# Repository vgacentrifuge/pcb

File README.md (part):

# VGA mixer PCB design
This repository contains the research and design work that went into the PCB
for our VGA mixer project in TDT4295 - computer project at NTNU, autumn 2022.

## Initial feasibility study
The [pdf](InitialFeasibilityStudy.pdf) contains the first research, before
the capabilities and requirements were fully fleshed out. In this repo,
we are working on the actual design.

## Project features
The VGA mixer is a device that takes two VGA inputs,
called "background" and "foreground", and outputs a single VGA video stream.

It should support the SVGA resolution 800x600 @ 60Hz and 16-bit color depth.
The colors are stored as (5,6,5)-bit RGB values internally.

On the board there are several buttons and an LCD screen,
allowing you to pick between different **modes**:
 - Showing only the foreground
 - Showing only the background
 - Overlaying with chroma keying appied to the foreground
 - Showing the foreground at 25%, 50% or 75% transparancy
 - Adding the colors (double exposure)

In addition to modes, the foreground can also be **scaled** and **translated**:
 - A button lets you pick between 100%, 50% and 25% size of the foreground.
 - Directional buttons allow you to move the foreground around

Finally, the foreground video input can be replaced by a still image loaded
from an SD card. Chroma keying can still be applied, to create borders or overlays.

TODO: Should we be able to save images, or is having a bank of overlays enough?

The LCD allows the user to orchestrate the modes and options to create quick
transitions, and saving states.

## Implementation overview
Both the background and foreground VGA signals get converted into digial pixel color values.
ADC chips do the conversion, and an FPGA reads the digital data.

The background video signal is never scaled or translated, and can be sent
almost directly out to the output DAC.
The output signal is just a few pixels behind the background.

The foreground gets buffered, either in SRAM or the FPGA's internal block RAM.
When the background signal is passing through the FPGA, it knows which pixel it is processing.
By checking its settings, it will know if and where the foreground framebuffer should be sampled.
Translations and scaling affect how the foreground overlays the background.

Scaling is done by doubling or quadrupling the current pixel coordinate (left shifting).
Translations are done by adding offsets. If the resulting pixel position
is still within the framebuffer bounds, it gets sampled.

Chroma key is handled by looking at the color chanels.
Transparancy is done by averaging the foreground and background layers.
To get 25% foreground, pixel = (fg+(fg<<1) + bg) >> 2, or something similar.
We don't want to do actual division.

User input is handled by an MCU, which is connected to the FPGA via SPI.
The MCU also handles the VGA input data pins, to communicate to our video sources
what resolution we support.

The SD card is also connected to the MCU over another SPI.
We use FAT32 formatted SD-cards, allowing the user to prepare overlays on their computer, saved as bmp.
See [this project here](https://create.arduino.cc/projecthub/SurtrTech/display-bmp-pictures-from-sd-card-on-tft-lcd-shield-f3074c).
The MCU does all file system work and image decoding. The LCD can be used to pick images by file name.
When selected, the foreground input gets ignored, and the FPGA fills the framebuffer with the image instead, sent over SPI.

In general, the MCU takes user input and uses SPI to send a state struct to the FPGA.
This means timed transitions, and switching between saved states, can be orchestrated from there.
Note that the MCU doesn't have enough RAM to store even a single frame.

## Components
This section contains the components we will need to place on the PCB.

### FPGA
We are working with the Artix-7 series, see the [Series Overview](https://docs.xilinx.com/v/u/en-US/ds180_7Series_Overview).

#### Dev-board
The [ARTY A7 development board](https://digilent.com/reference/programmable-logic/arty-a7/reference-manual) has an **ARTIX-7 XC7A35T** which has
 - 33280 logic cells
 - 50 blocks of 36Kib dual port block ram = 1 800Kib
 - 5 clock management tiles (CMTs), each with a phase-locked loop and mixed-mode clock manager
 - Programmable over JTAG or Quad-SPI Flash
 
The dev-board itself contains:
 - 256MB DDR3L with a 16-bit bus @ 667MHz
 - 16MB Quad-SPI Flash
 
#### On PCB
On the PCB we will use the **ARTIX-7 XC7A100T** in FTG256 package, which has already been procured.
 - 4,860 Kib of dual port block ram
 
See the data sheet for it [here](https://docs.xilinx.com/v/u/en-US/ds181_Artix_7_Data_Sheet),
and remember the user guides listed in the pcb lecture.

#### Voltages
The FPGA requires:
 - 1.0V (Vccint & Vccbram)
 - 1.8V (Vccaux)
 - 3.3V (Vcco) The standard signal voltage we use for I/O banks.

They must become ready in order, Vccint and Vccbram can rise together. 
For one bank, Vcco=1.8V, and the datasheet said it's fine to rise it together with Vccaux.

#### Required FPGA support components
In the datasheet they define that certain sets of **decoupling capacitors** should be connected to certain pins.
This is already included in the example schematic from the lecture.
Try to get them close to the pins on the actual PCB.

We also need a **configuration flash chip** on the board,
to program the FPGA on startup. See UG908 Appendix C.
We picked the one from the pcb lecture: [S25FL127SABMFV101](https://www.digikey.no/en/products/detail/cypress-semiconductor-corp/S25FL127SABMFV101/5788556).

#### FPGA's own clock signal
To not completly rely on the MCU's clockout,
The [arty schematic](https://digilent.com/reference/_media/arty:arty_sch.pdf) has and
[ASEM1-100.000MHZ-LC-T](https://no.mouser.com/ProductDetail/ABRACON/ASEM1-100.000MHZ-LC-T?qs=3KFUwL3kAg3Sbz4Re5NI5g%3D%3D), but it's not in stock.

We use the [EC2620TTS-100.000MTR](https://no.mouser.com/ProductDetail/Ecliptek-Abracon/EC2620TTS-100.000M-TR?qs=ZQxglWs2YhXyVb5B6v%252BGOw%3D%3D).

I checked the Xilinx Clocking Wizard, both MMCM and PLL will happily turn 100MHz into 160MHz.

#### Debug connector
The Debug connector from the lecture looks like the **14-pin F JTAG ILA connector**.
See [this website](https://developer.arm.com/documentation/100765/0000/Signal-descriptions/Debug-connectors/14-pin-F-JTAG-ILA-connector).
The pitch is 2mm, yes you read that right.
The component, through hole, can be found here:
[0878311411](https://www.digikey.no/en/products/detail/molex/0878311411/3313107).

See the example setup from the lecture (remember 2x 10k pullups).
However, this website says that pin 6 (TCK) is pulled down on their board,
**why is ours pulled up?** 

### SRAM
We need to calculate the required SRAM size.
With an 800x600=480 000 pixel grid, 16 bit color depth, it makes sense to
use a 512K x 16 bit SRAM. We do however also want to make the SRAM easy to address.

800 pixels of X-coordinate rounds up to 10 bits.
600 pixels of Y-coordinate also rounds up to 10 bits.
A 20 bit address means 2^20 = 1M x 16bit SRAM.

This size would also allow us to support 1024x768 (XGA),
but speed is a bigger issue. XGA has a pixel clock of 15.3ns / pixel.

To get good speed, we have looked at the syncronous 1M x 18b SRAM [CY7C1372KV33-200AXC](https://www.digikey.no/en/products/detail/cypress-semiconductor-corp/CY7C1372KV33-200AXC/5982740)
which supposedly costs 94kr per chip. It takes 3.3V.
With pipelining, the access time becomes 3ns,
with each operation delayed for two cycles.

The number of pins needed becomes:
 - 20 address pins
 - 18 data pins
 - write enable
 - clock
 - chip select
 - output enable

We use chip select to deselect, which when we don't need access.
The deselect is pipelined as well, allowing us to mix it into the operations.

We want to connect output enable to be sure that we never try to
write to th data line while it is being driven.
If we do everything perfectly, The data line is automatically tri-stated by writes,
but we want to be safe.

The rest, like output enable, clock enable, byte enable, advance etc. can all be pulled by the pcb.
This SRAM package does not expose JTAG pins.

### MCU
Available in the lab is the EFM32GG990F1024-BGA112
 - ARM Cortex M3
 - Flash: 1024kB
 - RAM: 128kB
 - USB support
 - ADC: 8 channels, 12 bit
 - DAC: 2 channels, 12 bit
 - SPI: 3
 - I2C: 2
 - GPIO: 87
 - 112 pin BGA package
 
For PCB considerations, see [SiLabs EFM32 AN0002](https://www.silabs.com/documents/public/application-notes/an0002.0-efm32-ezr32-series-0-hardware-design-considerations.pdf).
It includes decoupling capacitors. See Figure 3.1. EFM32 Series 0 Standard Decoupling Example.
Also add the 1 Ohm resistor from Figure 3.3.

#### MCU Debug connector

In the PCB lecture, they use the 2.54mm pitch legacy JTAG.
The debug conenctor is 20-pin header, shown in section 4 of AN0002.

Since we have a gecko with the modern connector, we can use the
modern [Cortex Debug+ETM Connector](https://documentation-service.arm.com/static/5fce6c49e167456a35b36af1).
It has 1.27mm pitch, we pick this through-hole one: [3220-20-0100-00](https://www.digikey.no/en/products/detail/cnc-tech/3220-20-0100-00/3883663).

#### MCU Clock circuit
By using an external crystal, as recommended, we can run the MCU at 48MHz.

<!--
This is simply buying a crystal oscillator.
The [FO7HSCDE48.0-T1](https://www.digikey.no/no/products/detail/fox-electronics/FO7HSCDE48-0-T1/12160237)
is 48MHz, SMD, and with 5mm and 2.5mm between the 4 pins, which at least isn't the smallest oscillator.
The datasheet also has recommended solder pad distance of at least 2.2 mm. Seems doable.
-->

The first chip we bought was in fact not a crystal, but an oscialltor chip using a crystal insternally.
We buy another one instead, see the schematic.

The AN0002 EFM32 hardware design considerations also mentions two capacitors.
The lecture uses 2x 12pF.

The FPGA can take the **clock out** signal from the EMF32GG as a clock input, and use phase-locked loops
to internally run faster clocks at rational multiples of the input.
We should also have a clock circuit on the FPGA side, so that we have two options.

### Connections
We use SPI between MCU and FPGA, and between MCU and SD-card. They can be fully independent.
For our SPI communication, the lecture tells us to add extra wires between the MCU and PCB for safety.

[I2C](https://en.wikipedia.org/wiki/I%C2%B2C) is "open drain", which means we must use pull-up resistors on the lines.
Calculations can be found in this [EFM32GG application note](https://www.silabs.com/documents/public/application-notes/AN0011.pdf).

We use I2C for the LCD, and I2C for the ADCs.
They both seem to like 400kHz, which means a 2kOhm resistor is common.
They both also want to be pulled up to 3.3V.

Between the boards, if we do make two PCBs, we want to connect them.
We can buy e.g. 2 of the 2x8 pin vertical male header per board [3020-16-0200-00](https://www.digikey.no/en/products/detail/cnc-tech/3020-16-0200-00/3441735).
And 2 of the female as well [PPPC082LJBN-RC](https://www.digikey.no/en/products/detail/sullins-connector-solutions/PPPC082LJBN-RC/776019).
These are both through-hole.

### Splitting the MCU and FPGA
We have considered splitting the PCB in half, to separate the MCU from the FPGA.
In practice we will probably not create two PCBs,
since clock lines shouldn't go through pins,
but it would be great to have a PCB that can be used
without the MCU physically on the board.

With SPI, we control the speed ourselves, so we can tune it down until it is stable,
depending on how the wiring is.

The SPI between the MCU and FPGA should have room to solder on a pin header.
The SPI clock is slower than the 48MHz clock-out from the MCU,
which should **not** have a pin header.
We also give the FPGA its own oscillator, to not depend on the MCU clock out.

The SPI lane for the SD card can also have holes for soldering on a pin header if desired.
The I2C buses for the ADCs and LCD screen should have pins,
and the keyboard matrix should have them.

### Power circuit
We base it on the PCB lecture. We need to power up the 1.0V, 1.8V and 3.3V in order.
The MCU and SD card use 3.3V, so does the SRAM.
The ADC uses 1.9V, and HSYNC and VSYNC must be level switched to / from 5V.

**Remember the jumpers** between the power circuit and rest of the board.
We buy a 2x5 male 2.54mm pin header [3020-10-0300-00](https://www.digikey.no/en/products/detail/cnc-tech/3020-10-0300-00/3441727), and
the 2x5 female jumper shunt, [69145-210LF](https://www.digikey.no/en/products/detail/amphenol-cs-fci/69145-210LF/1528094), with 3A rating per pin.

### SD-card & SD-card slot
We want a slot to be able to move the SD-card to and from a computer.
When connected, the MCU communicates via SPI to the card.
In addition to the 4 SPI pins, The SD-card takes a 3.3V VDD and ground.

See for instance [this website](https://www.electroniccircuitsdesign.com/pinout/sd-microsd-card-pinout.html) for pinout on the physical SD and microSD cards.

Note that [this SO-post](https://electronics.stackexchange.com/questions/496357/sd-card-via-spi-pull-up-resistors-or-dedicated-ic)
talks about pull-up resistors on all the data pins, we can do that too.

People seem to disagree, but hooking up a 10k Ohm resistor to each of DAT0-DAT3 and CMD seems good.
Also a 0.1 uF decoupling capacitor between Vcc and GND.

To easily solder, we can buy the [10067847-001RLF](https://www.digikey.no/no/products/detail/amphenol-cs-fci/10067847-001RLF/2283478).
It is full size SD, with solder pins visible

We should buy an SD card as well, the 512MB microSD [5252](https://www.digikey.no/en/products/detail/adafruit-industries-llc/5252/15841478) is cheap,
so buy at least one.

### LCD text output
A cheap 2 row x 16 char width LCD screen is [DFR0555](https://www.digikey.no/no/products/detail/dfrobot/DFR0555/9356340).
It is controlled over I2C.
8-bit address for LCD: 0x7C = 0b 0111 110X
8-bit address for backlight: 0xC0 = 0b 1100 000X
At 87mm x 32mm total, it is quite small. Each char is 2.96mm x 5.56mm.
Mouser doesn't have anything cheaper using I2C, so it's probably a good option.

### Input panel
We need to design a button layout that fits our functionality,
but also allows us to experiment after the PCB design is finalized.

We can use an off the shelf keyboard matrix, and re-label the keys.
Mouser stocks 81 of the 4x4 [3844](https://no.mouser.com/ProductDetail/Adafruit/3844?qs=qSfuJ%252Bfl%2Fd6WS5%252BJGim1hw%3D%3D).

### VGA ports
We need the physical VGA ports, as well as supporting components.
The speed we target is [SVGA 800x600@60Hz](http://tinyvga.com/vga-timing/800x600@60Hz).

The VGA connector itself is [described here](http://www.hardwarebook.info/VGA).
For VGA output we only really need to connect 5 pins, plus ground:
 - red, green, blue color (analog 0-0.7V, 75 Ohm)
 - horizontal sync, vertical sync (5V). See timing chart.

Note: While we are in the "porch" and sync pulse areas of the signal, the color values must all be 0V.
See for example the 2nd [Ben Eater VGA video](https://www.youtube.com/watch?v=uqY3FMuMuRo).

We also might want to connect the 3 DDC2B ports, in case we want to read info about the output monitor.
See the following sections about DAC and VGA Display Data Channel.

For inputs, we need to read those 5 signals, including the analog color signals (using ADCs).
We should also let the video sources get info about our board over I2C. See next sections.

As for the physical VGA ports, there is [L77HDE15SD1CH4FVGA](https://www.digikey.no/no/products/detail/amphenol-icc-commercial-products/L77HDE15SD1CH4FVGA/4888525) on digikey at 15kr a pop. Is has through-hole pins. Buy 9, 3 per PCB.

#### VGA Display Data Channel
The [DDC2B](https://en.wikipedia.org/wiki/Display_Data_Channel#DDC2) standard is an I2C protocol to communicate information about the "monitor" to the video source.

For the output port, we can connect the DDC pins to one of the MCU's I2C ports,
in case we want to read info about the screen.
NOTE: The I2C lines are open drain, and expect to be pulled up to 5V.
We will need a level shifter for the MCU to be able to use the I2C port.

##### VGA DDC level switches
The VGA standard expects 5V I2C over the SDA and SCL lines.
Both when we are slave and master, we want to support this.
Since all other I2C components use 3.3V, we level switch.

[This guide](https://cdn-shop.adafruit.com/datasheets/an97055.pdf)
shows how a single N-channel MOSFET does the trick.
We buy 2 per DDC I2C, 6 per board.
We pick the one they mention that is easiest to solder: [BSN20](https://www.digikey.no/en/products/detail/diodes-incorporated/BSN20-7/2756034).

<!--
For the three DDC channels, we can use one of
[771-LSF0102DCH](https://no.mouser.com/ProductDetail/Nexperia/LSF0102DCH?qs=zW32dvEIR3vhhHCS5E8Gjg%3D%3D)
for each.

If you are curious how open-drain interfaces, like I2C, work through it,
[this datasheet](https://www.ti.com/lit/ds/symlink/lsf0102.pdf?ts=1663455770501)
for a similar device has an example in section 9.2.
-->

#### VGA HSYNC VSYNC Level shifters
They come in at 5V, but must be 3.3V into the ADC.
Same applies to the output VGA, but the other way.
We don't use the DAC's HSYNC and VSYNC ports,
instead letting the FPGA control it.
It would be nice to support 1.8V input, since the rest of video out is at 1.8V.

For each ADC, and for the output, buy one
[771-LSF0102DCH](https://www.digikey.no/no/products/detail/nexperia-usa-inc/LSF0102DCH/13574967).

##### Input VGA ports: I2C EEPROMs
On our VGA inputs, we should respond to I2C read commands, to return 128-256 bytes of read only [Extended Display Identification Data](https://en.wikipedia.org/wiki/Extended_Display_Identification_Data).
See [this page](http://www.hardwarebook.info/VGA_(VESA_DDC)) for specifications.
The VGA DDC uses three pins: I2C data, I2C clock, and DC +5V delivered by the video source.
Our board must respond to the 7-bit I²C address 50h (also known as A0h and A1h in 8-bit).

To save having to use our MCU from needing to be a slave over the VGA ports, we can buy dirt cheep I2C EEPROMSs.
For instance [M24C02-WMN6TP](https://www.digikey.no/no/products/detail/stmicroelectronics/M24C02-WMN6TP/1663568),
in stock at Digikey.no, at 1,7kr a piece. They work at 2.5V - 5.5V, and we use one per VGA input = 6 for 3 boards.

Note: The EEPROMs technically support running on 5V,
and the VGA port has 5V supplied by the graphics card.
The reason we don't want to use it is that the graphics card
expects us to draw < 1mA when the monitor is on.

In DDC, the I2C master will try to read from address 0xA1 = 0b1010 0001.
This is perfect! The EEPROM listens for address 0b1010 XXXX, where
we configure the first 3 X's ourselves. The last bit is 1 for read and 0 for write.

##### I2C EEPROM support components
 - Vcc should be decoupled "usually of the order of 10 nF to 100 nF, close to the Vcc/Vss pins".
 - E0, E1 and E2 should be connected to ground, to listen to the correct address.
 
 - We should create a jumper thing to let the MCU be the programmer, if we ever need to change the EEPROM.
 - It should have 5 pins:
   - Vcc (3.3V)
   - Vss
   - SCL
   - SDA
   - Write enable (just connect to Vss to enable writing)
 
 Opposite to it there should be the same 5 pins comming from one of the MCU's I2C buses,
 e.g. the one used to configure the ADCs.
 
 To make the connector easy, we can use a 3x5 pin header, and have the MCU connected
 to the middle row, and jump either to the left or right.
 See [TSW-105-07-F-T](https://www.digikey.no/en/products/detail/samtec-inc/TSW-105-07-F-T/6692070).

#### Input VGA ADCs
The analog color inputs of each VGA input needs to become digital 6 or 5 bit values.
We can use ADCs with more bit depth than this, and then ignore the least significant bits.

The video ADC we looked at is the 3 channel x 10bit TI [TVP7002PZPR](https://no.mouser.com/ProductDetail/Texas-Instruments/TVP7002PZPR?qs=0OHPnBYoB%2FnBqXV%2Fq5aVXw%3D%3D)

It is configurable over I2C, things like gain, clamp and offset. Also programmable subpixel positioning.
It also has a PLL on the HSYNC, allowing it to generate a pixel clock for the FPGA VGA inputs.
The 40MHz on SVGA is well within the 12-165MHz range.

So: **we need to connect the ADCs to the MCU, to program them**.
Luckily, the chips have one bit of customizable address, so the options are:
 - 0xB8 = 0b10111000
 - 0xBA = 0b10111010
Remember that the last bit is 1 for read and 0 for write.
Notably, neither of these addresses collide with the 0xA0/0xA1 of the VGA DDC,
but you have to remember voltages.

The ADC needs 3.3V and **1.9V**!

The I/O is however 3.3V, so we can connect it to a "normal" FPGA bank.

But: VGA HSYNC and VSYNC are 5V signals. We can **not** pass those into the ADC!
See the HSYNC VSYNC Level shifter section above.

##### ADC support components
See the example setup in the datasheets.

- 1x (=2x) ADC support
     - 3x (=6x) Sync-on-green input disable: 1nF capacitor
     - 7x (=14x) 10nF capacitors for unused analog input
     - 1x (=2x) PLL pump
       - 1x (=2x) Resistor 1.5kOhm
       - 1x (=2x) Capacitor 4.7nF
       - 1x (=2x) Capacitor 0.1uF
   - 1x (=2x) I2C address choice: Resistor 2.2kOhm
   - 3x (=6x) Color inputs
     - 1x (=6x) 75 Ohm resistors
     - 1x (=6x) 0.1 uF capacitors
   - 1x (=2x) VSYNC parallel 1nF capacitor
   - even more stuff, just look at the suggested schematic

#### Output VGA DAC
When outputing analog color data, we don't want to use resistors, as they take space,
and the FPGA outputs are not the best at delivering DC current.

A nice DAC that Mouser stocks is  [THS8136IPHP](https://no.mouser.com/ProductDetail/Texas-Instruments/THS8136IPHP?qs=h8kCHL4kpM5MDIol0WiuLg%3D%3D)
It has 3 10-bit inputs named R, G and B, and 180MS/s.
For 800x600 @ 60Hz, a throughput of at least 40 MSPS is enough.
It takes 3.3V analog, and 1.8V digital.
**This means the FPGA pins delivering VGA out must be 1.8V**.
Luckily, when the Vcco is the same as Vccaux (1.8V), they can be ramped at the same time.

 - 0.1 uF decoupling capacitors near each power pin (3 of them)
 - 0.1 uF capacitors between COMP-AVdd and between VREF-AVss
 - R_FS between FSADJ and AVss. TODO
 - 3x 75 Ohm resistors, for each analog output? TODO

It also has [PCB Layout Guidelines](https://www.ti.com/lit/an/slea077/slea077.pdf?ts=1663284093618).
10x trace width clearance between analog inputs.
Everything close! Resistors, capacitors, analog output port.
TODO: ESD protection on the analog outputs is recommended.

#### Protection
We buy TVS diodes like the [PUSB3AB2DF](https://www.digikey.no/en/products/detail/nexperia-usa-inc/PUSB3AB2DFZ/12325057?s=N4IgTCBcDaIAoFUDKAhAzAQRWAIgMRAF0BfIA).

## Development components
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
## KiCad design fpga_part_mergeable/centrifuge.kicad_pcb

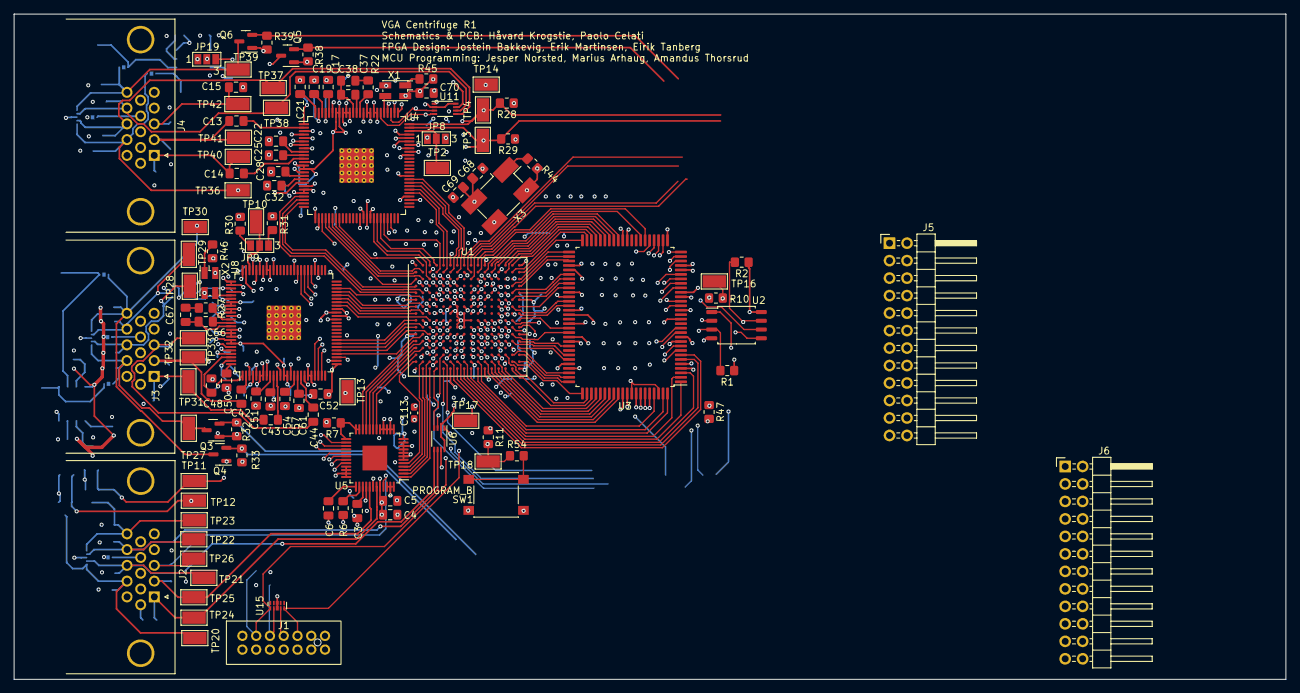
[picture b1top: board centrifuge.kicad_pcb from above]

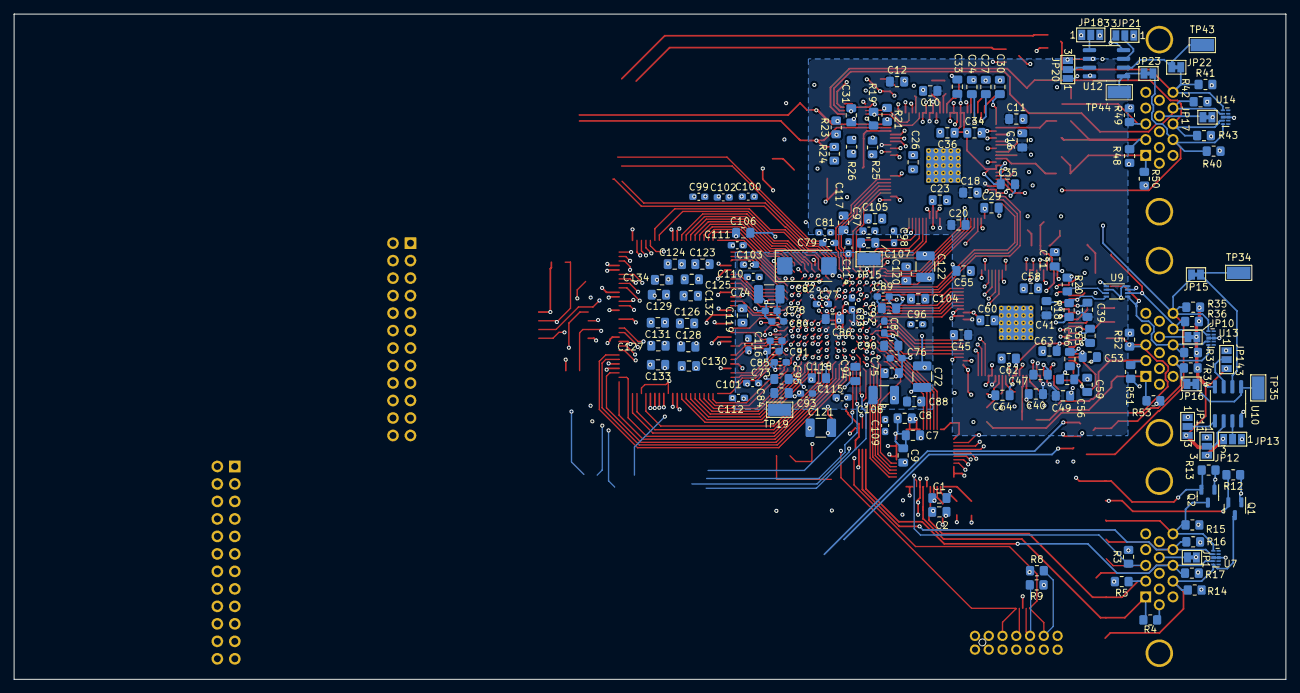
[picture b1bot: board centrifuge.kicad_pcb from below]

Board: 6 copper layers, 184.8 x 96.6 mm, 274 parts (163 on the bottom side), 265 nets.

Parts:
C1, C2, C7, C8: 10u; C_0805_2012Metric_Pad1.18x1.45mm_HandSolder
C3, C4, C5, C6, C9, C13, C14, C15, C20, C31, C36, C38, C42, C43, C44, C49, C60, C65, C67, C70, C71, C123, C124, C125, C126, C127, C128, C129, C130, C131, C132, C133, C134: 0.1u; C_0805_2012Metric_Pad1.18x1.45mm_HandSolder
C10, C11, C12, C16, C18, C23, C26, C29, C33, C34, C35, C39, C40, C41, C45, C47, C52, C55, C58, C62, C63, C64: 1u; C_0805_2012Metric_Pad1.18x1.45mm_HandSolder
C17, C19, C21, C22, C25, C28, C32, C46, C48, C50, C51, C54, C57, C61, C68: 10n; C_0805_2012Metric_Pad1.18x1.45mm_HandSolder
C24, C27, C30, C53, C56, C59: 1n; C_0805_2012Metric_Pad1.18x1.45mm_HandSolder
C37, C66: 4.7n; C_0805_2012Metric_Pad1.18x1.45mm_HandSolder
C69: 0.1u tantalum; C_0805_2012Metric_Pad1.18x1.45mm_HandSolder
C72, C108, C121, C122: 47u X5R/X7R; C_1210_3225Metric_Pad1.33x2.70mm_HandSolder
C73, C75, C84, C86, C88, C90, C92, C94, C104, C105, C106, C107, C117, C118, C119, C120: 4.7u; C_0805_2012Metric_Pad1.18x1.45mm_HandSolder
C74: 100u tantalum 1-40 mOhm or X5R/X7R; C_1210_3225Metric_Pad1.33x2.70mm_HandSolder
C76, C77, C78, C79, C80, C81, C83, C85, C87, C89, C91, C93, C95, C96, C97, C98, C99, C100, C101, C102, C103, C109, C110, C111, C112, C113, C114, C115, C116: 470n; C_0603_1608Metric_Pad1.08x0.95mm_HandSolder
C82: 330u tantalum 5-40 mOhm; CP_EIA-7343-31_Kemet-D_Pad2.25x2.55mm_HandSolder
J1: Conn_02x07_Odd_Even; 878311411
J2, J3, J4: Conn_01x15; L77HDE15SD1CH4FVGA
J5, J6: Conn_02x12_Odd_Even; PinHeader_2x12_P2.54mm_Horizontal
JP1, JP10, JP15, JP16, JP17, JP22, JP23: Jumper_2_Bridged; SolderJumper-2_P1.3mm_Bridged_Pad1.0x1.5mm
JP8, JP9: Jumper_3_Open; SolderJumper-3_P1.3mm_Open_Pad1.0x1.5mm_NumberLabels
JP11, JP12, JP13, JP14, JP18, JP19, JP20, JP21: SolderJumper_3_Bridged12; SolderJumper-3_P1.3mm_Open_Pad1.0x1.5mm_NumberLabels
Q1, Q2, Q3, Q4, Q5, Q6: BSN20; SOT-23
R1, R2, R11, R47: 4.7k; R_0805_2012Metric_Pad1.20x1.40mm_HandSolder
R3, R4, R5, R48, R49, R50, R51, R52, R53: 75; R_0805_2012Metric_Pad1.20x1.40mm_HandSolder
R6: 3.8k; R_0805_2012Metric_Pad1.20x1.40mm_HandSolder
R7, R23, R24, R25, R26, R28, R29, R30, R31: 2.2k; R_0805_2012Metric_Pad1.20x1.40mm_HandSolder
R8, R9, R44, R45, R46: 10k; R_0805_2012Metric_Pad1.20x1.40mm_HandSolder
R10, R54: 330; R_0805_2012Metric_Pad1.20x1.40mm_HandSolder
R12, R32, R38: vga_ddc_sda_pullup_l; R_0805_2012Metric_Pad1.20x1.40mm_HandSolder
R13, R33, R39: vga_ddc_scl_pullup_l; R_0805_2012Metric_Pad1.20x1.40mm_HandSolder
R14, R34, R40: vga_ddc_sda_pullup_h; R_0805_2012Metric_Pad1.20x1.40mm_HandSolder
R15, R35, R41: vga_ddc_scl_pullup_h; R_0805_2012Metric_Pad1.20x1.40mm_HandSolder
R16, R17, R18, R19, R20, R21, R36, R37, R42, R43: 1k; R_0805_2012Metric_Pad1.20x1.40mm_HandSolder
R22, R27: 1.5k; R_0805_2012Metric_Pad1.20x1.40mm_HandSolder
SW1: SW_MEC_5E; SW_Push_1P1T_NO_6x6mm_H9.5mm_modified
TP2, TP3, TP4, TP10, TP11, TP12, TP13, TP14, TP15, TP16, TP17, TP18, TP19, TP20, TP21, TP22, TP23, TP24, TP25, TP26, TP27, TP28, TP29, TP30, TP31, TP32, TP33, TP34, TP35, TP36, TP37, TP38, TP39, TP40, TP41, TP42, TP43, TP44: TestPoint; TestPoint_Keystone_5015_Micro-Minature
U1: XC7A100T-FTG256; Xilinx_FTG256
U2: S25FL127SABMFV10; SOIC-8_5.23x5.23mm_P1.27mm
U3: CY7C1370KV33; PQFP-100_14x20mm_P0.65mm
U4, U8: TVP7002; TQFP-100-1EP_14x14mm_P0.5mm_EP5x5mm_ThermalVias_elprint
U5: THS8136; LQFP-48-1EP_7x7mm_P0.5mm_EP3.6x3.6mm
U6, U9, U11: LSF0102; VSSOP-8_2.3x2mm_P0.5mm
U7, U13, U14: PESD4USB5B-TTS; Diodes_UDFN-10_1.0x2.5mm_P0.5mm
U10, U12: M24C02-WMN; SOIC-8_3.9x4.9mm_P1.27mm
U15: D5V0FS4U10LP; Diodes_UDFN-10_1.0x2.5mm_P0.5mm
X1, X2: ECS-2333-270-BN; Oscillator_SMD_EuroQuartz_XO32-4Pin_3.2x2.5mm_HandSoldering
X3: EC2620TTS-100.000MTR; Oscillator_SMD_EuroQuartz_XO91-4Pin_7.0x5.0mm_HandSoldering

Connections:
+1V0: C74.1, C76.1, C78.1, C80.1, C82.1, C83.1, C84.1, C85.1, C86.1, C87.1, C88.1, C89.1, C90.1, C91.1, C92.1, C93.1, C94.1, C95.1, TP15.1, TP17.1, TP19.1, U1.E10 (VCCBRAM), U1.F7 (VCCINT), U1.F9 (VCCINT), U1.F11 (VCCBRAM), U1.G6 (VCCINT), U1.H9 (VCCINT), U1.J6 (VCCINT), U1.K9 (VCCINT), U1.L8 (VCCINT)
+1V8_FPGA: C7.1, C8.1, C9.1, C72.1, C73.1, C75.1, C77.1, C79.1, C81.1, C96.1, C98.1, C100.1, C102.1, C104.1, C106.1, C108.1, J1.2, J5.8, R7.1, TP13.1, TP14.1, U1.G8 (VCCADC_0), U1.G10 (VCCAUX), U1.J10 (VCCAUX), U1.K11 (VCCAUX), U1.L10 (VCCAUX), U1.M3 (VCCO_34), U1.R4 (VCCO_34), U1.T1 (VCCO_34), U5.12 (DVDD), U6.2 (refA), U6.8 (EN), U9.2 (refA), U9.8 (EN), U11.2 (refA), U11.8 (EN)
+1V9_FPGA: C10.1, C11.1, C12.1, C16.1, C18.1, C20.1, C39.1, C40.1, C41.1, C45.1, C47.1, C49.1, J5.10, U4.4 (AVDD), U4.6 (AVDD), U4.7 (AVDD), U4.19 (AVDD), U4.39 (DVDD), U4.69 (DVDD), U4.84 (PLL_AVDD), U4.85 (PLL_AVDD), U8.4 (AVDD), U8.6 (AVDD), U8.7 (AVDD), U8.19 (AVDD), U8.39 (DVDD), U8.69 (DVDD), U8.84 (PLL_AVDD), U8.85 (PLL_AVDD)
+3V3A_FPGA: C33.1, C34.1, C35.1, C36.1, C62.1, C63.1, C64.1, C65.1, J5.6, U4.13 (A33VDD), U4.14 (A33VDD), U4.93 (A33VDD), U4.94 (A33VDD), U8.13 (A33VDD), U8.14 (A33VDD), U8.93 (A33VDD), U8.94 (A33VDD)
+3V3_FPGA: C1.1, C2.1, C4.1, C5.1, C23.1, C26.1, C29.1, C31.1, C52.1, C55.1, C58.1, C60.1, C68.1, C69.1, C70.1, C71.1, C97.1, C99.1, C101.1, C103.1, C105.1, C107.1, C109.1, C110.1, C111.1, C112.1, C113.1, C114.1, C115.1, C116.1, C117.1, C118.1, C119.1, C120.1, C121.1, C122.1, C123.1, C124.1, C125.1, C126.1, C127.1, C128.1, C129.1, C130.1, C131.1, C132.1, C133.1, C134.1, J5.4, Q1.1 (G), Q2.1 (G), Q3.1 (G), Q4.1 (G), Q5.1 (G), Q6.1 (G), R1.1, R2.1, R8.1, R9.1, R10.1, R11.1, R12.1, R13.1, R18.1, R19.1, R20.1, R21.1, R23.1, R24.1, R25.1, R28.1, R29.1, R30.1, R32.1, R33.1, R38.1, R39.1, R44.1, R45.1, R46.1, R47.1, U1.A6 (VCCO_35), U1.A16 (VCCO_15), U1.B3 (VCCO_35), U1.B13 (VCCO_15), U1.C10 (VCCO_15), U1.D7 (VCCO_35), U1.E4 (VCCO_35), U1.E7 (CFGBVS_0), U1.E14 (VCCO_15), U1.F1 (VCCO_35), U1.H15 (VCCO_15), U1.J2 (VCCO_35), U1.J12 (VCCO_15), U1.L6 (VCCO_0), U1.L16 (VCCO_14), U1.M9 (M0_0), U1.M13 (VCCO_14), U1.N10 (VCCO_14), U1.P7 (VCCO_14), U1.R14 (VCCO_14), U1.T11 (VCCO_14), U2.8 (VCC), U3.4 (VDDQ), U3.11 (VDDQ), U3.15 (VDD), U3.20 (VDDQ), U3.27 (VDDQ), U3.41 (VDD), U3.54 (VDDQ), U3.61 (VDDQ), U3.65 (VDD), U3.70 (VDDQ), U3.77 (VDDQ), U3.91 (VDD), U4.26 (IOVDD), U4.41 (IOVDD), U4.53 (IOVDD), U4.66 (IOVDD), U5.40 (AVDD), U5.44 (AVDD), U8.26 (IOVDD), U8.41 (IOVDD), U8.53 (IOVDD), U8.66 (IOVDD), X1.4 (VDD), X2.4 (VDD), X3.4 (VDD)
+5V_FPGA: J5.2, JP1.1 (A), JP10.1 (A), JP11.3 (B), JP12.3 (B), JP13.3 (B), JP14.3 (B), JP17.1 (A), JP18.3 (B), JP19.3 (B), JP20.3 (B), JP21.3 (B), R14.2, R15.2, R16.1, R17.1, R34.2, R35.2, R36.1, R37.1, R40.2, R41.2, R42.1, R43.1, U6.7 (refB), U9.7 (refB), U10.8 (VCC), U11.7 (refB), U12.8 (VCC)
/CONFIG_DONE: J5.21, R10.2, TP16.1, U1.H10 (DONE_0)
/INIT_B: J5.19, R47.2, U1.K10 (INIT_B_0)
/MCU_ADC0_RST: J5.5, U4.71 (RESETB)
/MCU_ADC1_RST: J5.11, U8.71 (RESETB)
/PROGRAM_B: J5.17, R11.2, R54.1, TP18.1, U1.L9 (PROGRAM_B_0)
/SCL_MCU_MASTER: J5.9, Q2.2 (S), R13.2, R24.2, R29.2, TP3.1, TP11.1, U4.74 (SCL), U8.74 (SCL)
/SCL_MCU_SL0: J5.1, Q6.2 (S), R39.2
/SCL_MCU_SL1: J5.13, Q4.2 (S), R33.2
/SDA_MCU_MASTER: J5.7, Q1.2 (S), R12.2, R23.2, R28.2, TP4.1, TP12.1, U4.75 (SDA), U8.75 (SDA)
/SDA_MCU_SL0: J5.3, Q5.2 (S), R38.2
/SDA_MCU_SL1: J5.15, Q3.2 (S), R32.2
/fpga_part/AUXIO1: J6.17, U1.K12 (IO_0_14)
/fpga_part/AUXIO2: J6.19, U1.M14 (IO_L4N_T0_D05_14)
/fpga_part/AUXIO3: J6.21, U1.K13 (IO_L5P_T0_D06_14)
/fpga_part/AUXIO4: J6.23, U1.M12 (IO_L6N_T0_D08_VREF_14)
/fpga_part/AUXIO5: J6.24, U1.P10 (IO_L14P_T2_SRCC_14)
/fpga_part/AUXIO6: J6.22, U1.P11 (IO_L14N_T2_SRCC_14)
/fpga_part/AUXIO7: J6.20, U1.N9 (IO_L18P_T2_A12_D28_14)
/fpga_part/AUXIO8: J6.18, U1.P9 (IO_L18N_T2_A11_D27_14)
/fpga_part/AUXIO9: J6.16, U1.R5 (IO_L23P_T3_A03_D19_14)
/fpga_part/AUXIO10: J6.14, U1.T5 (IO_L23N_T3_A02_D18_14)
/fpga_part/AUXIO11: J6.12, U1.P6 (IO_25_14)
/fpga_part/AUXIO12: J6.10, U1.J15 (IO_L23P_T3_FOE_B_15)
/fpga_part/AUXIO13: J6.8, U1.B9 (IO_L3P_T0_DQS_AD1P_15)
/fpga_part/AUXIO14: J6.6, U1.A9 (IO_L2N_T0_AD8N_15)
/fpga_part/AUXIO15: J6.4, U1.A8 (IO_L2P_T0_AD8P_15)
/fpga_part/AUXIO16: J6.2, U1.C9 (IO_L1N_T0_AD0N_15)
/fpga_part/AUXIO17L: J6.1, U1.P5 (IO_L10P_T1_34)
/fpga_part/AUXIO18: J6.3, U1.C4 (IO_L12N_T1_MRCC_35)
/fpga_part/AUXIO19: J6.5, U1.D4 (IO_L12P_T1_MRCC_35)
/fpga_part/AUXIO20: J6.7, U1.D5 (IO_L6N_T0_VREF_35)
/fpga_part/AUXIO21: J6.9, U1.D6 (IO_L6P_T0_35)
/fpga_part/AUXIO22: J6.11, U1.C6 (IO_L5N_T0_AD13N_35)
/fpga_part/AUXIO23: J6.13, U1.C7 (IO_L5P_T0_AD13P_35)
/fpga_part/AUXIO24: J6.15, U1.E6 (IO_0_35)
/fpga_part/config_sram/CCLK: U1.E8 (CCLK_0), U2.6 (CLK)
/fpga_part/config_sram/GCLK100: U1.C13 (IO_L12N_T1_MRCC_15), X3.3 (OUT)
/fpga_part/config_sram/IO0: U1.J13 (IO_L1P_T0_D00_MOSI_14), U2.5 (SI/IO0)
/fpga_part/config_sram/IO1: U1.J14 (IO_L1N_T0_D01_DIN_14), U2.2 (SO/IO1)
/fpga_part/config_sram/IO2: R1.2, U1.K15 (IO_L2P_T0_D02_14), U2.3 (n_WP/IO2)
/fpga_part/config_sram/IO3: R2.2, U1.K16 (IO_L2N_T0_D03_14), U2.7 (n_HOLD/IO3)
/fpga_part/config_sram/SRAM_A0: U1.B10 (IO_L4P_T0_15), U3.37 (A0)
/fpga_part/config_sram/SRAM_A1: U1.A10 (IO_L3N_T0_DQS_AD1N_15), U3.36 (A1)
/fpga_part/config_sram/SRAM_A2: U1.C11 (IO_L11P_T1_SRCC_15), U3.35 (A)
/fpga_part/config_sram/SRAM_A3: U1.C12 (IO_L11N_T1_SRCC_15), U3.34 (A)
/fpga_part/config_sram/SRAM_A4: U1.D11 (IO_L14N_T2_SRCC_15), U3.33 (A)
/fpga_part/config_sram/SRAM_A5: U1.E12 (IO_L13P_T2_MRCC_15), U3.32 (A)
/fpga_part/config_sram/SRAM_A6: U1.B12 (IO_L5P_T0_AD9P_15), U3.44 (A)
/fpga_part/config_sram/SRAM_A7: U1.A13 (IO_L7P_T1_AD2P_15), U3.45 (A)
/fpga_part/config_sram/SRAM_A8: U1.A14 (IO_L7N_T1_AD2N_15), U3.46 (A)
/fpga_part/config_sram/SRAM_A9: U1.B14 (IO_L8N_T1_AD10N_15), U3.47 (A)
/fpga_part/config_sram/SRAM_A10: U1.A15 (IO_L9N_T1_DQS_AD3N_15), U3.48 (A)
/fpga_part/config_sram/SRAM_A11: U1.B15 (IO_L9P_T1_DQS_AD3P_15), U3.49 (A)
/fpga_part/config_sram/SRAM_A12: U1.B16 (IO_L10N_T1_AD11N_15), U3.50 (A)
/fpga_part/config_sram/SRAM_A13: U1.T9 (IO_L22P_T3_A05_D21_14), U3.100 (A)
/fpga_part/config_sram/SRAM_A14: U1.T10 (IO_L22N_T3_A04_D20_14), U3.99 (A)
/fpga_part/config_sram/SRAM_A15: U1.T14 (IO_L10P_T1_D14_14), U3.84 (A)
/fpga_part/config_sram/SRAM_A16: U1.T15 (IO_L10N_T1_D15_14), U3.83 (A)
/fpga_part/config_sram/SRAM_A17: U1.P14 (IO_L12N_T1_MRCC_14), U3.82 (A)
/fpga_part/config_sram/SRAM_A18: U1.R15 (IO_L9P_T1_DQS_14), U3.81 (A)
/fpga_part/config_sram/SRAM_A19: U1.B11 (IO_L4N_T0_15), U3.42 (NC(72))
/fpga_part/config_sram/SRAM_A20: U1.A12 (IO_L5N_T0_AD9N_15), U3.43 (NC(36))
/fpga_part/config_sram/SRAM_ADV_LD: U1.R13 (IO_L16P_T2_CSI_B_14), U3.85 (ADV/~LD)
/fpga_part/config_sram/SRAM_CE1: U1.P8 (IO_L20P_T3_A08_D24_14), U3.92 (~CE3), U3.98 (~CE1)
/fpga_part/config_sram/SRAM_CE2: U1.R10 (IO_L17P_T2_A14_D30_14), U3.97 (CE2)
/fpga_part/config_sram/SRAM_CEN: U1.R12 (IO_L15P_T2_DQS_RDWR_B_14), U3.87 (~CEN)
/fpga_part/config_sram/SRAM_CLK: U1.R11 (IO_L17N_T2_A13_D29_14), U3.89 (CLK)
/fpga_part/config_sram/SRAM_D0: U1.H16 (IO_L22P_T3_A17_15), U3.63 (DQa)
/fpga_part/config_sram/SRAM_D1: U1.G15 (IO_L24N_T3_RS0_15), U3.62 (DQa)
/fpga_part/config_sram/SRAM_D2: U1.G16 (IO_L22N_T3_A16_15), U3.59 (DQa)
/fpga_part/config_sram/SRAM_D3: U1.F15 (IO_L18P_T2_A24_15), U3.58 (DQa)
/fpga_part/config_sram/SRAM_D4: U1.E16 (IO_L17P_T2_A26_15), U3.57 (DQa)
/fpga_part/config_sram/SRAM_D5: U1.E15 (IO_L18N_T2_A23_15), U3.56 (DQa)
/fpga_part/config_sram/SRAM_D6: U1.D16 (IO_L17N_T2_A25_15), U3.53 (DQa)
/fpga_part/config_sram/SRAM_D7: U1.D15 (IO_L15N_T2_DQS_ADV_B_15), U3.52 (DQa)
/fpga_part/config_sram/SRAM_D8: U1.C16 (IO_L10P_T1_AD11P_15), U3.51 (DQPa)
/fpga_part/config_sram/SRAM_D9: U1.C14 (IO_L8P_T1_AD10P_15), U3.30 (DQPd)
/fpga_part/config_sram/SRAM_D10: U1.D13 (IO_L12P_T1_MRCC_15), U3.29 (DQd)
/fpga_part/config_sram/SRAM_D11: U1.D14 (IO_L15P_T2_DQS_15), U3.28 (DQd)
/fpga_part/config_sram/SRAM_D12: U1.E13 (IO_L13N_T2_MRCC_15), U3.25 (DQd)
/fpga_part/config_sram/SRAM_D13: U1.F13 (IO_L16N_T2_A27_15), U3.24 (DQd)
/fpga_part/config_sram/SRAM_D14: U1.F14 (IO_L21N_T3_DQS_A18_15), U3.23 (DQd)
/fpga_part/config_sram/SRAM_D15: U1.G14 (IO_L21P_T3_DQS_15), U3.22 (DQd)
/fpga_part/config_sram/SRAM_D16: U1.H14 (IO_L24P_T3_RS1_15), U3.19 (DQd)
/fpga_part/config_sram/SRAM_D17: U1.H13 (IO_L20N_T3_A19_15), U3.18 (DQd)
/fpga_part/config_sram/SRAM_D18: U1.L14 (IO_L4P_T0_D04_14), U3.13 (DQc)
/fpga_part/config_sram/SRAM_D19: U1.L13 (IO_L5N_T0_D07_14), U3.12 (DQc)
/fpga_part/config_sram/SRAM_D20: U1.N13 (IO_L11P_T1_SRCC_14), U3.9 (DQc)
/fpga_part/config_sram/SRAM_D21: U1.P13 (IO_L11N_T1_SRCC_14), U3.8 (DQc)
/fpga_part/config_sram/SRAM_D22: U1.R6 (IO_L24P_T3_A01_D17_14), U3.7 (DQc)
/fpga_part/config_sram/SRAM_D23: U1.T7 (IO_L21P_T3_DQS_14), U3.6 (DQc)
/fpga_part/config_sram/SRAM_D24: U1.R7 (IO_L24N_T3_A00_D16_14), U3.3 (DQc)
/fpga_part/config_sram/SRAM_D25: U1.R8 (IO_L20N_T3_A07_D23_14), U3.2 (DQc)
/fpga_part/config_sram/SRAM_D26: U1.T8 (IO_L21N_T3_DQS_A06_D22_14), U3.1 (DQPc)
/fpga_part/config_sram/SRAM_D27: U1.R16 (IO_L9N_T1_DQS_D13_14), U3.80 (DQPb)
/fpga_part/config_sram/SRAM_D28: U1.P16 (IO_L8N_T1_D12_14), U3.79 (DQb)
/fpga_part/config_sram/SRAM_D29: U1.P15 (IO_L8P_T1_D11_14), U3.78 (DQb)
/fpga_part/config_sram/SRAM_D30: U1.N16 (IO_L7N_T1_D10_14), U3.75 (DQb)
/fpga_part/config_sram/SRAM_D31: U1.M15 (IO_L3N_T0_DQS_EMCCLK_14), U3.74 (DQb)
/fpga_part/config_sram/SRAM_D33: U1.M16 (IO_L7P_T1_D09_14), U3.72 (DQb)
/fpga_part/config_sram/SRAM_D34: U1.L15 (IO_L3P_T0_DQS_PUDC_B_14), U3.69 (DQb)
/fpga_part/config_sram/SRAM_D35: U1.J16 (IO_L23N_T3_FWE_B_15), U3.68 (DQb)
/fpga_part/config_sram/SRAM_OE: U1.T13 (IO_L16N_T2_A15_D31_14), U3.86 (~OE)
/fpga_part/config_sram/SRAM_WE: U1.T12 (IO_L15N_T2_DQS_DOUT_CSO_B_14), U3.88 (~WE)
/fpga_part/config_sram/n_CONFIG_CS: U1.L12 (IO_L6P_T0_FCS_B_14), U2.1 (~CS)
/fpga_part/e1/B: C44.2, J3.3, R52.1, TP33.1
/fpga_part/e1/B5: U1.J1 (IO_L22N_T3_35), U8.33 (B_5)
/fpga_part/e1/B6: U1.K2 (IO_L24N_T3_35), U8.32 (B_6)
/fpga_part/e1/B7: U1.K1 (IO_L22P_T3_35), U8.31 (B_7)
/fpga_part/e1/B8: U1.L3 (IO_L23P_T3_35), U8.30 (B_8)
/fpga_part/e1/B9: U1.L2 (IO_L23N_T3_35), U8.29 (B_9)
/fpga_part/e1/DCLK_OUT: U1.F5 (IO_L13P_T2_MRCC_35), U8.28 (DATACLK)
/fpga_part/e1/FIDOUT: U1.J4 (IO_L19N_T3_VREF_35), U8.22 (FIDOUT)
/fpga_part/e1/G: C42.2, J3.2, R51.1, TP32.1
/fpga_part/e1/G4: U1.F2 (IO_L15P_T2_DQS_35), U8.48 (G_4)
/fpga_part/e1/G5: U1.G2 (IO_L17P_T2_35), U8.47 (G_5)
/fpga_part/e1/G6: U1.G1 (IO_L17N_T2_35), U8.46 (G_6)
/fpga_part/e1/G7: U1.H2 (IO_L20P_T3_35), U8.45 (G_7)
/fpga_part/e1/G8: U1.H1 (IO_L20N_T3_35), U8.44 (G_8)
/fpga_part/e1/G9: U1.J3 (IO_L21P_T3_DQS_35), U8.43 (G_9)
/fpga_part/e1/HSIN: R18.2, U8.81 (HSYNC_A), U9.4 (A2)
/fpga_part/e1/HSOUT: U1.K3 (IO_L24P_T3_35), U8.24 (HSOUT)
/fpga_part/e1/R: C43.2, J3.1, R53.1, TP31.1
/fpga_part/e1/R5: U1.H4 (IO_L18N_T2_35), U8.59 (R_5)
/fpga_part/e1/R6: U1.H5 (IO_L18P_T2_35), U8.58 (R_6)
/fpga_part/e1/R7: U1.H3 (IO_L21N_T3_DQS_35), U8.57 (R_7)
/fpga_part/e1/R8: U1.G4 (IO_L16N_T2_35), U8.56 (R_8)
/fpga_part/e1/R9: U1.F4 (IO_L14P_T2_SRCC_35), U8.55 (R_9)
/fpga_part/e1/VSIN: R20.2, U8.78 (VSYNC_A), U9.3 (A1)
/fpga_part/e1/VSOUT: U1.J5 (IO_L19P_T3_35), U8.23 (VSOUT)
/fpga_part/e2/B: C15.2, J4.3, R49.1, TP42.1
/fpga_part/e2/B5: U1.A2 (IO_L8N_T1_AD14N_35), U4.33 (B_5)
/fpga_part/e2/B6: U1.B2 (IO_L8P_T1_AD14P_35), U4.32 (B_6)
/fpga_part/e2/B7: U1.B1 (IO_L9N_T1_DQS_AD7N_35), U4.31 (B_7)
/fpga_part/e2/B8: U1.C2 (IO_L7N_T1_AD6N_35), U4.30 (B_8)
/fpga_part/e2/B9: U1.C1 (IO_L9P_T1_DQS_AD7P_35), U4.29 (B_9)
/fpga_part/e2/DCLK_OUT: U1.E5 (IO_L13N_T2_MRCC_35), U4.28 (DATACLK)
/fpga_part/e2/FIDOUT: U1.E1 (IO_L15N_T2_DQS_35), U4.22 (FIDOUT)
/fpga_part/e2/G: C13.2, J4.2, R48.1, TP41.1
/fpga_part/e2/G4: U1.D3 (IO_L11N_T1_SRCC_35), U4.48 (G_4)
/fpga_part/e2/G5: U1.E3 (IO_L11P_T1_SRCC_35), U4.47 (G_5)
/fpga_part/e2/G6: U1.B4 (IO_L4P_T0_35), U4.46 (G_6)
/fpga_part/e2/G7: U1.A4 (IO_L3N_T0_DQS_AD5N_35), U4.45 (G_7)
/fpga_part/e2/G8: U1.A3 (IO_L4N_T0_35), U4.44 (G_8)
/fpga_part/e2/G9: U1.C3 (IO_L7P_T1_AD6P_35), U4.43 (G_9)
/fpga_part/e2/HSIN: R19.2, U4.81 (HSYNC_A), U11.4 (A2)
/fpga_part/e2/HSOUT: U1.D1 (IO_L10N_T1_AD15N_35), U4.24 (HSOUT)
/fpga_part/e2/R: C14.2, J4.1, R50.1, TP40.1
/fpga_part/e2/R5: U1.B7 (IO_L1P_T0_AD4P_35), U4.59 (R_5)
/fpga_part/e2/R6: U1.A7 (IO_L1N_T0_AD4N_35), U4.58 (R_6)
/fpga_part/e2/R7: U1.B6 (IO_L2P_T0_AD12P_35), U4.57 (R_7)
/fpga_part/e2/R8: U1.B5 (IO_L2N_T0_AD12N_35), U4.56 (R_8)
/fpga_part/e2/R9: U1.A5 (IO_L3P_T0_DQS_AD5P_35), U4.55 (R_9)
/fpga_part/e2/VSIN: R21.2, U4.78 (VSYNC_A), U11.3 (A1)
/fpga_part/e2/VSOUT: U1.E2 (IO_L10P_T1_AD15P_35), U4.23 (VSOUT)
/fpga_part/e3/SCL: JP15.1 (A), TP34.1, U10.6 (SCL)
/fpga_part/e3/SDA: JP16.1 (A), TP35.1, U10.5 (SDA)
/fpga_part/e4/SCL: JP22.1 (A), TP43.1, U12.6 (SCL)
/fpga_part/e4/SDA: JP23.1 (A), TP44.1, U12.5 (SDA)
/fpga_part/e/B5: U1.R1 (IO_L7N_T1_34), U5.5 (B5)
/fpga_part/e/B6: U1.R2 (IO_L7P_T1_34), U5.4 (B6)
/fpga_part/e/B7: U1.T2 (IO_L8N_T1_34), U5.3 (B7)
/fpga_part/e/B8: U1.R3 (IO_L8P_T1_34), U5.2 (B8)
/fpga_part/e/B9: U1.T3 (IO_L9N_T1_DQS_34), U5.1 (B9)
/fpga_part/e/B_OUT: J2.3, R3.1, TP26.1, U5.45 (AB)
/fpga_part/e/COMP: C3.1, U5.39 (COMP)
/fpga_part/e/DAC_CLK: U1.L4 (IO_L1P_T0_34), U5.26 (CLK)
/fpga_part/e/FSADJ: R6.1, U5.38 (FSADJ)
/fpga_part/e/G4: U1.M5 (IO_L6P_T0_34), U5.32 (G4)
/fpga_part/e/G5: U1.P4 (IO_L5P_T0_34), U5.31 (G5)
/fpga_part/e/G6: U1.N4 (IO_L6N_T0_VREF_34), U5.30 (G6)
/fpga_part/e/G7: U1.P3 (IO_L5N_T0_34), U5.29 (G7)
/fpga_part/e/G8: U1.M4 (IO_L1N_T0_34), U5.28 (G8)
/fpga_part/e/G9: U1.N3 (IO_L3P_T0_DQS_34), U5.27 (G9)
/fpga_part/e/G_OUT: J2.2, R5.1, TP25.1, U5.41 (AG)
/fpga_part/e/R5: U1.P1 (IO_L4N_T0_34), U5.18 (R5)
/fpga_part/e/R6: U1.N2 (IO_L3N_T0_DQS_34), U5.19 (R6)
/fpga_part/e/R7: U1.N1 (IO_L4P_T0_34), U5.20 (R7)
/fpga_part/e/R8: U1.M2 (IO_L2P_T0_34), U5.21 (R8)
/fpga_part/e/R9: U1.M1 (IO_L2N_T0_34), U5.22 (R9)
/fpga_part/e/R_OUT: J2.1, R4.1, TP24.1, U5.43 (AR)
/fpga_part/e/SYNC_T: R7.2, U5.23 (~BLANK), U5.24 (~SYNC), U5.25 (SYNC_T)
/fpga_part/e/VREF: C6.1, U5.37 (VREF)
/fpga_part/fpga_core/HSYNC_OUT0: U1.L5 (IO_0_34), U6.3 (A1)
/fpga_part/fpga_core/VSYNC_OUT0: U1.T4 (IO_L9P_T1_DQS_34), U6.4 (A2)
/fpga_part/pwr_jtag/TCK: J1.6, R9.2, U1.L7 (TCK_0), U15.2 (CH2)
/fpga_part/pwr_jtag/TDI: J1.10, U1.N7 (TDI_0), U15.5 (CH4)
/fpga_part/pwr_jtag/TDO: J1.8, U1.N8 (TDO_0), U15.4 (CH3)
/fpga_part/pwr_jtag/TMS: J1.4, R8.2, U1.M7 (TMS_0), U15.1 (CH1)
/fpga_part/vga_interface1/HSYNC_H: J3.13, R37.2, TP28.1, U9.5 (B2), U13.4 (CH3)
/fpga_part/vga_interface1/SCL_H: J3.15, JP15.2 (B), Q4.3 (D), R35.1, TP30.1, U13.1 (CH1)
/fpga_part/vga_interface1/SDA_H: J3.12, JP16.2 (B), Q3.3 (D), R34.1, TP27.1, U13.5 (CH4)
/fpga_part/vga_interface1/VSYNC_H: J3.14, R36.2, TP29.1, U9.6 (B1), U13.2 (CH2)
/fpga_part/vga_interface2/HSYNC_H: J4.13, R43.2, TP37.1, U11.5 (B2), U14.4 (CH3)
/fpga_part/vga_interface2/SCL_H: J4.15, JP22.2 (B), Q6.3 (D), R41.1, TP39.1, U14.1 (CH1)
/fpga_part/vga_interface2/SDA_H: J4.12, JP23.2 (B), Q5.3 (D), R40.1, TP36.1, U14.5 (CH4)
/fpga_part/vga_interface2/VSYNC_H: J4.14, R42.2, TP38.1, U11.6 (B1), U14.2 (CH2)
/fpga_part/vga_interface/HSYNC_H: J2.13, R17.2, TP21.1, U6.5 (B2), U7.4 (CH3)
/fpga_part/vga_interface/SCL_H: J2.15, Q2.3 (D), R15.1, TP23.1, U7.1 (CH1)
/fpga_part/vga_interface/SDA_H: J2.12, Q1.3 (D), R14.1, TP20.1, U7.5 (CH4)
/fpga_part/vga_interface/VSYNC_H: J2.14, R16.2, TP22.1, U6.6 (B1), U7.2 (CH2)
EP_GND: C1.2, C2.2, C3.2, C4.2, C5.2, C6.2, C7.2, C8.2, C9.2, C10.2, C11.2, C12.2, C16.2, C17.2, C18.2, C19.2, C20.2, C21.2, C22.2, C23.2, C24.2, C25.2, C26.2, C27.2, C28.2, C29.2, C30.2, C31.2, C32.2, C33.2, C34.2, C35.2, C36.2, C39.2, C40.2, C41.2, C45.2, C46.2, C47.2, C48.2, C49.2, C50.2, C51.2, C52.2, C53.2, C54.2, C55.2, C56.2, C57.2, C58.2, C59.2, C60.2, C61.2, C62.2, C63.2, C64.2, C65.2, C68.2, C69.2, C70.2, C71.2, C72.2, C73.2, C74.2, C75.2, C76.2, C77.2, C78.2, C79.2, C80.2, C81.2, C82.2, C83.2, C84.2, C85.2, C86.2, C87.2, C88.2, C89.2, C90.2, C91.2, C92.2, C93.2, C94.2, C95.2, C96.2, C97.2, C98.2, C99.2, C100.2, C101.2, C102.2, C103.2, C104.2, C105.2, C106.2, C107.2, C108.2, C109.2, C110.2, C111.2, C112.2, C113.2, C114.2, C115.2, C116.2, C117.2, C118.2, C119.2, C120.2, C121.2, C122.2, C123.2, C124.2, C125.2, C126.2, C127.2, C128.2, C129.2, C130.2, C131.2, C132.2, C133.2, C134.2, J1.1, J1.3, J1.5, J1.7, J1.9, J1.11, J1.13, J2.5, J2.6, J2.7, J2.8, J2.10, J3.5, J3.6, J3.7, J3.8, J3.10, J4.5, J4.6, J4.7, J4.8, J4.10, JP11.1 (A), JP12.1 (A), JP13.1 (A), JP14.1 (A), JP18.1 (A), JP19.1 (A), JP20.1 (A), JP21.1 (A), R3.2, R4.2, R5.2, R6.2, R26.2, R31.2, R48.2, R49.2, R50.2, R51.2, R52.2, R53.2, SW1.3 (K), SW1.4 (A), U1.A1 (GND), U1.A11 (GND), U1.B8 (GND), U1.C5 (GND), U1.C15 (GND), U1.D2 (GND), U1.D12 (GND), U1.E9 (GND), U1.F6 (GND), U1.F8 (VCCBATT_0), U1.F10 (GND), U1.F16 (GND), U1.G3 (GND), U1.G7 (GNDADC_0), U1.G9 (GND), U1.G13 (GND), U1.H6 (GND), U1.H7 (VREFN_0), U1.H8 (VP_0), U1.J7 (VN_0), U1.J8 (VREFP_0), U1.J9 (GND), U1.J11 (GND), U1.K4 (GND), U1.K6 (GND), U1.K7 (DXN_0), U1.K8 (DXP_0), U1.K14 (GND), U1.L1 (GND), U1.L11 (GND), U1.M8 (GND), U1.M10 (M1_0), U1.M11 (M2_0), U1.N5 (GND), U1.N15 (GND), U1.P2 (GND), U1.P12 (GND), U1.R9 (GND), U1.T6 (GND), U1.T16 (GND), U2.4 (GND), U3.5 (VSS), U3.10 (VSS), U3.17 (VSS), U3.21 (VSS), U3.26 (VSS), U3.31 (MODE), U3.40 (VSS), U3.55 (VSS), U3.60 (VSS), U3.64 (ZZ), U3.67 (VSS), U3.71 (VSS), U3.76 (VSS), U3.90 (VSS), U3.93 (~BWa), U3.94 (~BWb), U3.95 (~BWc), U3.96 (~BWd), U4.3 (AGND), U4.5 (AGND), U4.8 (AGND), U4.12 (A33GND), U4.15 (A33GND), U4.20 (AGND), U4.21 (NSUB), U4.27 (IOGND), U4.40 (GND), U4.42 (IOGND), U4.54 (IOGND), U4.60 (IOGND), U4.67 (IOGND), U4.68 (GND), U4.70 (PWDN), U4.72 (TMS), U4.76 (CLAMP), U4.77 (COAST), U4.79 (VSYNC_B), U4.82 (HSYNC_B), U4.83 (PLL_AGND), U4.86 (PLL_AGND), U4.90 (PLL_AGND), U4.91 (NSUB), U4.92 (A33GND), U4.95 (A33GND), U4.101 (EP_GND), U5.6 (B4), U5.7 (B3), U5.8 (B2), U5.9 (B1), U5.10 (B0), U5.11 (DVSS), U5.13 (R0), U5.14 (R1), U5.15 (R2), U5.16 (R3), U5.17 (R4), U5.33 (G3), U5.34 (G2), U5.35 (G1), U5.36 (G0), U5.42 (AVSS), U5.46 (AVSS), U5.47 (M1), U5.48 (M2), U6.1 (GND), U7.3 (GND), U7.8 (GND), U8.3 (AGND), U8.5 (AGND), U8.8 (AGND), U8.12 (A33GND), U8.15 (A33GND), U8.20 (AGND), U8.21 (NSUB), U8.27 (IOGND), U8.40 (GND), U8.42 (IOGND), U8.54 (IOGND), U8.60 (IOGND), U8.67 (IOGND), U8.68 (GND), U8.70 (PWDN), U8.72 (TMS), U8.76 (CLAMP), U8.77 (COAST), U8.79 (VSYNC_B), U8.82 (HSYNC_B), U8.83 (PLL_AGND), U8.86 (PLL_AGND), U8.90 (PLL_AGND), U8.91 (NSUB), U8.92 (A33GND), U8.95 (A33GND), U8.101 (EP_GND), U9.1 (GND), U10.4 (VSS), U11.1 (GND), U12.4 (VSS), U13.3 (GND), U13.8 (GND), U14.3 (GND), U14.8 (GND), U15.3 (GND), U15.8 (GND), X1.2 (GND), X2.2 (GND), X3.2 (GND)
unnamed: C13.1, U4.2 (GIN_1)
unnamed: C14.1, U4.11 (RIN_1)
unnamed: C15.1, U4.18 (BIN_1)
unnamed: C17.1, U4.96 (GIN_4)
unnamed: C19.1, U4.98 (GIN_3)
unnamed: C21.1, U4.100 (GIN_2)
unnamed: C22.1, U4.9 (RIN_3)
unnamed: C24.1, U4.97 (SOGIN_3)
unnamed: C25.1, U4.10 (RIN_2)
unnamed: C27.1, U4.99 (SOGIN_2)
unnamed: C28.1, U4.16 (BIN_3)
unnamed: C30.1, U4.1 (SOGIN_1)
unnamed: C32.1, U4.17 (BIN_2)
unnamed: C37.1, C38.1, U4.89 (PLL_F)
unnamed: C37.2, U4.88 (FILT2)
unnamed: C38.2, R22.1
unnamed: C42.1, U8.2 (GIN_1)
unnamed: C43.1, U8.11 (RIN_1)
unnamed: C44.1, U8.18 (BIN_1)
unnamed: C46.1, U8.96 (GIN_4)
unnamed: C48.1, U8.98 (GIN_3)
unnamed: C50.1, U8.100 (GIN_2)
unnamed: C51.1, U8.9 (RIN_3)
unnamed: C53.1, U8.97 (SOGIN_3)
unnamed: C54.1, U8.10 (RIN_2)
unnamed: C56.1, U8.99 (SOGIN_2)
unnamed: C57.1, U8.16 (BIN_3)
unnamed: C59.1, U8.1 (SOGIN_1)
unnamed: C61.1, U8.17 (BIN_2)
unnamed: C66.1, C67.1, U8.89 (PLL_F)
unnamed: C66.2, U8.88 (FILT2)
unnamed: C67.2, R27.1
unnamed: J2.9, JP1.2 (B)
unnamed: J3.9, JP10.2 (B)
unnamed: J4.9, JP17.2 (B)
unnamed: JP8.1 (A), R25.2
unnamed: JP8.2 (C), TP2.1, U4.73 (I2CA)
unnamed: JP8.3 (B), R26.1
unnamed: JP9.1 (A), R30.2
unnamed: JP9.2 (C), TP10.1, U8.73 (I2CA)
unnamed: JP9.3 (B), R31.1
unnamed: JP11.2 (C), U10.1 (E0)
unnamed: JP12.2 (C), U10.2 (E1)
unnamed: JP13.2 (C), U10.3 (E2)
unnamed: JP14.2 (C), U10.7 (~WC)
unnamed: JP18.2 (C), U12.1 (E0)
unnamed: JP19.2 (C), U12.2 (E1)
unnamed: JP20.2 (C), U12.3 (E2)
unnamed: JP21.2 (C), U12.7 (~WC)
unnamed: R22.2, U4.87 (FILT1)
unnamed: R27.2, U8.87 (FILT1)
unnamed: R44.2, X3.1 (Tri-State)
unnamed: R45.2, X1.1 (Tri-State)
unnamed: R46.2, X2.1 (Tri-State)
unnamed: R54.2, SW1.1, SW1.2
unnamed: U4.80 (EXT_CLK), X1.3 (OUT)
unnamed: U8.80 (EXT_CLK), X2.3 (OUT)
